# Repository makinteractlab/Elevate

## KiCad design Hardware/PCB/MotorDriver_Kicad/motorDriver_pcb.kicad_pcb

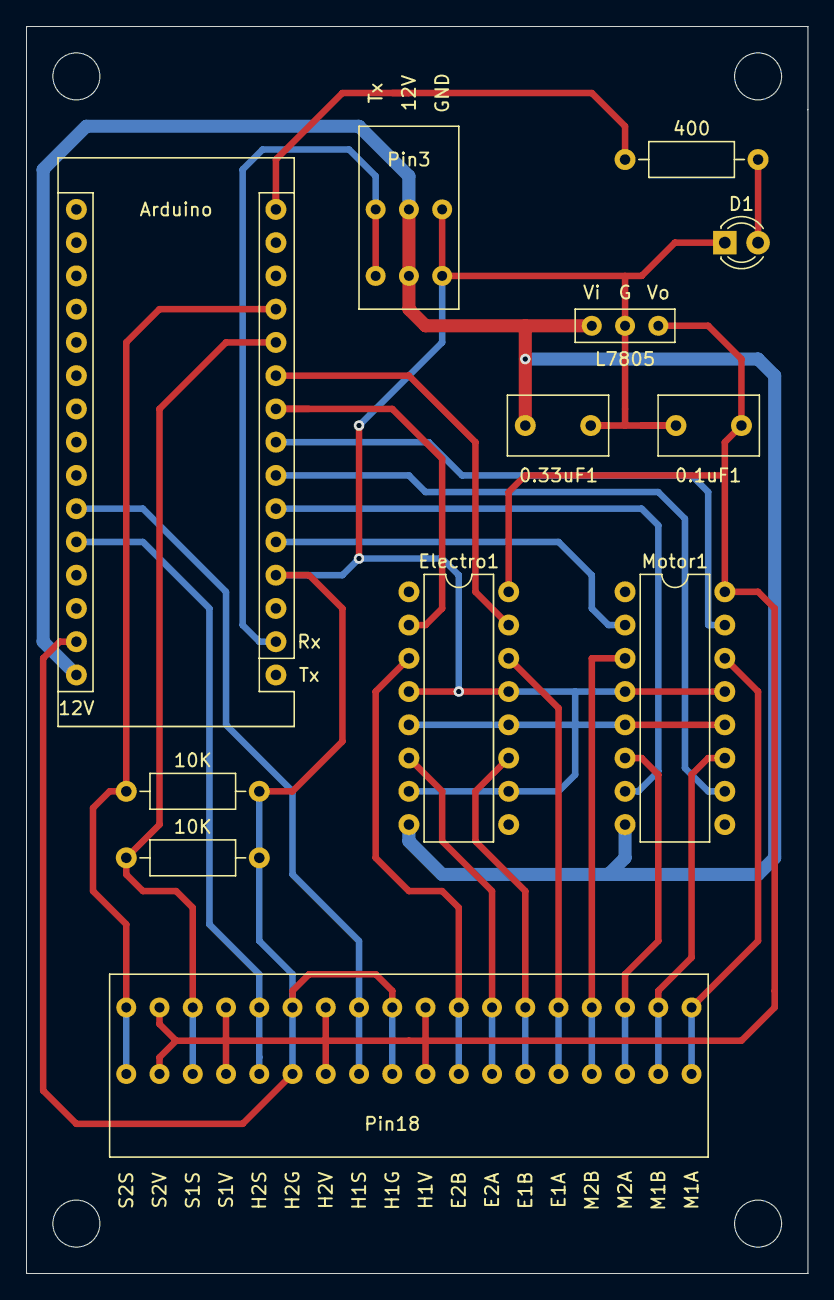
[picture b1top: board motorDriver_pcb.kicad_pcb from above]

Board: 2 copper layers, 59.7 x 95.2 mm, 12 parts (0 on the bottom side), 24 nets.

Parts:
0.1uF1: 0.1uF; C_Disc_D7.5mm_W4.4mm_P5.00mm
0.33uF1: 0.33uF; C_Disc_D7.5mm_W4.4mm_P5.00mm
10K, 10K#2: 10k; R_Axial_DIN0207_L6.3mm_D2.5mm_P10.16mm_Horizontal
400: 300; R_Axial_DIN0207_L6.3mm_D2.5mm_P10.16mm_Horizontal
Arduino: Arduino_Nano_v3.x; Arduino_Nano
D1: LED; LED_D3.0mm
Electro1: L293D; DIP-16_W7.62mm
L7805: L7805; Tip120
Motor1: L293D; DIP-16_W7.62mm
Pin3: Conn_01x03; 3pin_connector
Pin18: pin_connector; pin_18

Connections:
+5V: 0.1uF1.1, Electro1.16, L7805.3, Motor1.16, Pin18.9, Pin18.12, Pin18.15, Pin18.17
+12V: 0.33uF1.1, Arduino.30, Electro1.8, L7805.1, Motor1.8, Pin3.2
A6: Arduino.25, Pin18.11
A7: Arduino.26, Pin18.14
D2: Arduino.5, Motor1.2
D3: Arduino.6, Motor1.7
D4: Arduino.7, Motor1.10
D5: Arduino.8, Motor1.15
D6: Arduino.9, Electro1.2
D7: Arduino.10, Electro1.15
D8: 10K#2.1, Arduino.11, Pin18.16
D9: 10K.1, Arduino.12, Pin18.18
E1A: Electro1.14, Pin18.5
E1B: Electro1.11, Pin18.6
E2A: Electro1.6, Pin18.7
E2B: Electro1.3, Pin18.8
GND: 0.1uF1.2, 0.33uF1.2, 10K.2, 10K#2.2, Arduino.4, Arduino.29, D1.1, Electro1.4, Electro1.5, Electro1.7, Electro1.10, Electro1.12, Electro1.13, L7805.2, Motor1.4, Motor1.5, Motor1.12, Motor1.13, Pin3.1, Pin18.10, Pin18.13
M1A: Motor1.14, Pin18.1
M1B: Motor1.11, Pin18.2
M2A: Motor1.6, Pin18.3
M2B: Motor1.3, Pin18.4
unnamed: 400.1, Arduino.15
unnamed: 400.2, D1.2
Tx: Arduino.2, Pin3.3

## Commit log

2020-07-14 Hardware files and firmware 🐱‍👓
2020-07-14 Raycast scene with corrections. Adding Unity gitignores.
    Fixed the Unity Raycast scene. There seemed to be a race between Play's Start() and RayBasedFloor's Start(). To fix this, Play now uses Awake(), so that the playMatrix is complete before RayBasedFloo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
2020-07-14 Added foot tracking and floor manager aligns to left controller now.
2020-07-14 Added foot tracking.
2020-07-15 Add stairVR Application
2020-07-15 Add previous ControllerGUI Unity
2020-07-15 update stairVR Application
2020-07-22 Update ControllerGUI_Unity and New stairs in StairVR
2020-08-03 Play Script Update
2020-08-03 Msi Change(ignore)
2020-08-04 stairVR Update(Additional button for debug)
2020-08-04 Stepper Motor Update(change unit length)
2020-08-05 initial commit of minigolf app
2020-08-05 update JSON format
2020-08-05 fix hovering bug
2020-08-05 add pin debug
2020-08-11 add icons
2020-08-11 Play script. Corrected pin directions. Added masking.
    Updated Play scripts according to Hyunseung's code. Corrected the mirrored pins (I believe). Added masking.
2020-08-12 Unity Change(ignore)
2020-08-13 Add Hardware Evaluating Function
2020-08-13 Add Hardware Evaluating Function 2
2020-08-15 update coordinates and add arrow
2020-08-18 Add Locking Function
2020-08-18 Control Software Final Update
2020-08-18 major updates onWriteMatrix script-same format with Jas' code
2020-08-19 Corrected technical mistakes in step calculations. Removed adaptive height (now just uses target + height of pin). Need to fix real-world scaling.
2020-08-20 push before combining two projects
